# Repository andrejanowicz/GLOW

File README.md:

# GLOW preamp board for G&L L-2000 and L-2500 Tribute basses

</br>

### you might now the situation

>You’re at band rehearsal, playing your beautiful L2000 in active mode with crisp treble boost (that's how its done, right?), as you notice the dreaded hissing of a dying battery. You switch to passive mode with the swiftness of a hungry cheetah, but the guitar player already gives you the look. Of course he has noticed. He always does. You did only pretend to notice the pre CBS mojo of his '62 Strat though. Take that, Mr. all-passive-signal-path.
>
>As the song is done, you put the bass away. No way you’re changing the battery right here on the spot, with all those witnesses. This dirty secret must stay between the L2000 and you, they must not know! They have no idea that this is Leo’s actual masterpiece, not some overpriced 60s guitar. You touch the little switches, toggle them one by one, the click is as satisfying as on the day you brought it home. It takes some time to understand them, sure. To you, they are no mystery. Of course there are a lot of wires needed for all this flexibility, only a fool would not understand that. „Volume - Volume - Tone.. Pathetic!“ you mumble to yourself a little louder than intended. By now the drummer also looks at you. You go home. You wait until everybody is asleep and start silently searching for the screwdriver. You bite your tongue as you open the electronics compartment. You just can’t stand that mess. This instrument deserves better. You change the battery, put the bass aside and check to what dimensions the lead time for Wal MK2‘s has grown by now. You drool over that sweet, clean and well organized electronics box, that PCB: per-fec-tion. If you only bought one eight years ago, when you had the chance. While contemplating live decisions you hear a soft voice: Is everything okay, honey? It’s late, are you looking at bass guitars on the internet again? "Damn right I am, and I think I might have a plan" you say as you look up without blinking your eyes.

## Features

- single PCB with elegant black soldermask
- directly connected toggle switches, no extra wires
- additional single coil setting using only outer coils (K-Mod)
- original preamp circuitry using highest quality components:
- Wima MKP/FKP foil capacitors, Panasonic FC electrolytic capacitors, Yageo 1% resistors
- compatible with original LM4250 or alternatively TL061 op-amps
- fully open source KiCad project (CC BY-NC-SA 4.0)
- fits Tribute models made in Korea and Indonesia (no guarantee)
- banana shaped

## PCB top
</br>
## PCB bottom
</br>
## installed

I give absolutely no guarantee that the PCB and most important the position of the toggle switches will fit your bass. Glow was succesfully installed by me and others in four and five string indonesian and korean Tribute models (L-2000 and L-2500). Fit in USA models is unknown. It does <b>not</b> fit models with sheet metal cover on front/knob side. 
The stock 24mm pots are interfering with GLOW PCB and you need to use 16mm pots with at least 7mm thread length. For more information see BOM document.

## Drill hole position check

You can upfront assess the fit by 3D printing GLOW_test_jig.stl and align the jig with the position of your toggle switches.

## Thanks
This project would have been much harder without the extensive information found on [bassesbyleo.com](https://www.bassesbyleo.com/) .

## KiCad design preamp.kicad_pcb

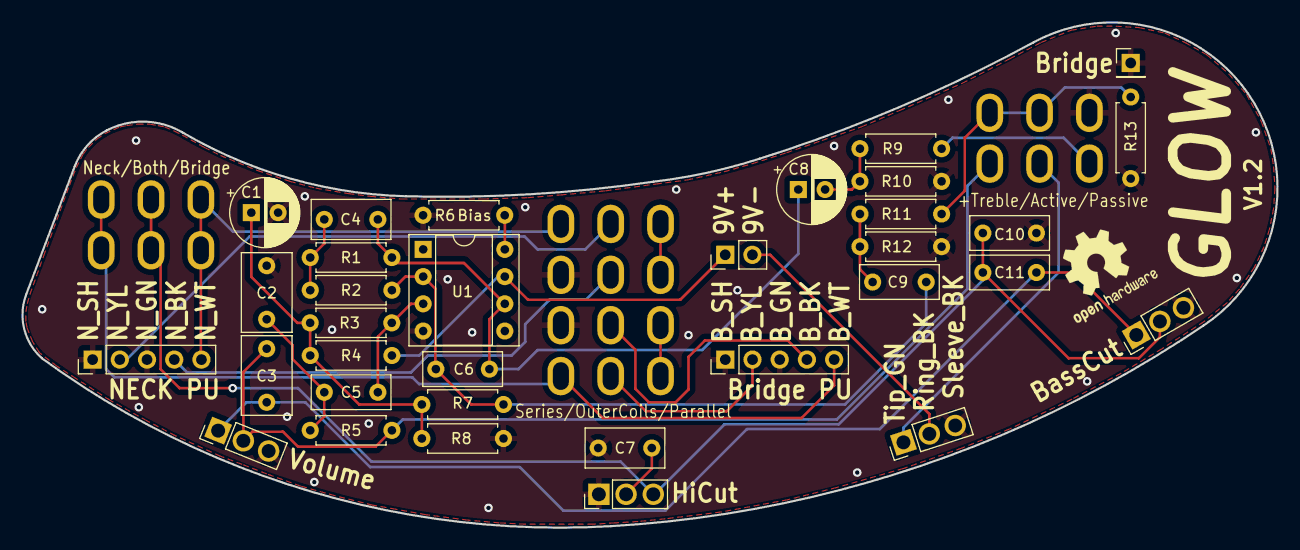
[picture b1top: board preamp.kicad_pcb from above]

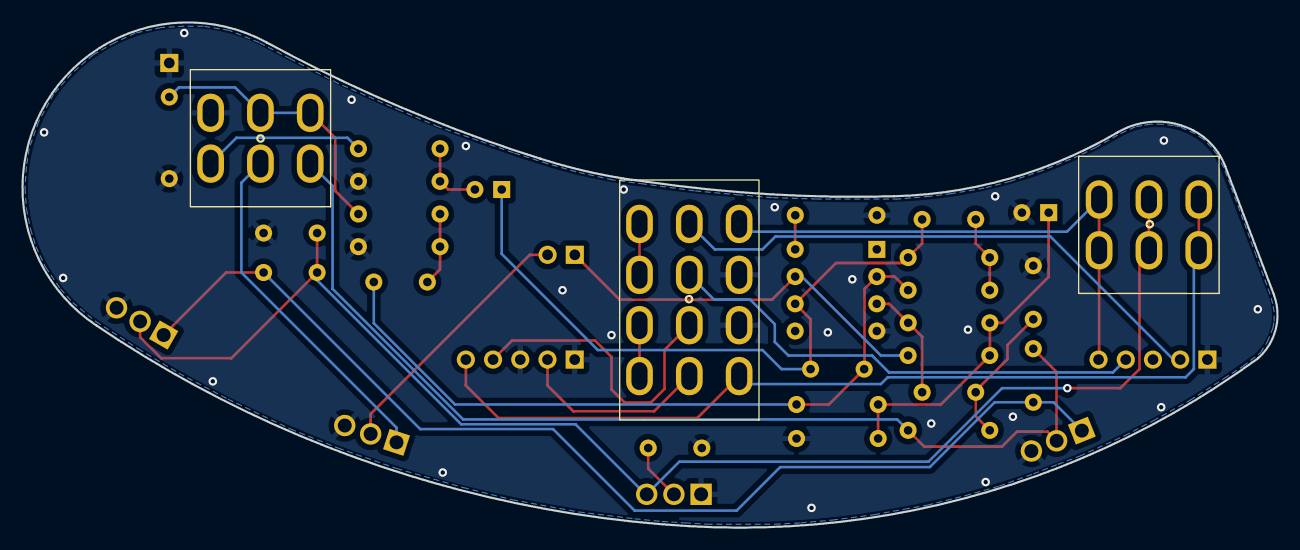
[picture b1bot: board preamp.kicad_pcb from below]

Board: 2 copper layers, 117.1 x 47.1 mm, 36 parts (3 on the bottom side), 27 nets.

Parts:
C1, C8: 10uF; CP_Radial_D6.3mm_P2.50mm
C2, C3: 220pF; C_Rect_L7.2mm_W4.5mm_P5.00mm_FKS2_FKP2_MKS2_MKP2
C4, C7: 47nF; C_Rect_L7.2mm_W3.5mm_P5.00mm_FKS2_FKP2_MKS2_MKP2
C5: 10nF; C_Rect_L7.2mm_W3.0mm_P5.00mm_FKS2_FKP2_MKS2_MKP2
C6, C10: 1nF; C_Rect_L7.2mm_W3.0mm_P5.00mm_FKS2_FKP2_MKS2_MKP2
C9: 15nF; C_Rect_L7.2mm_W3.0mm_P5.00mm_FKS2_FKP2_MKS2_MKP2
C11: 2,2nF; C_Rect_L7.2mm_W3.0mm_P5.00mm_FKS2_FKP2_MKS2_MKP2
J1: Neck; PinHeader_1x05_P2.54mm_Vertical
J2: Bridge; PinHeader_1x05_P2.54mm_Vertical
J3: 9V; PinHeader_1x02_P2.54mm_Vertical
J4: TRS; PinHeader_1x03_P2.54mm_Vertical
J5: Bridge GND; PinHeader_1x01_P2.54mm_Vertical
P1: Volume 250k log; PinHeader_1x03_P2.54mm_Vertical
P2: Hi Cut 250k log; PinHeader_1x03_P2.54mm_Vertical
P3: Bass Cut 1M; PinHeader_1x03_P2.54mm_Vertical
R1, R2: 21.5k; R_Axial_DIN0207_L6.3mm_D2.5mm_P7.62mm_Horizontal
R3, R4, R8: 1M; R_Axial_DIN0207_L6.3mm_D2.5mm_P7.62mm_Horizontal
R5, R9: 1k; R_Axial_DIN0207_L6.3mm_D2.5mm_P7.62mm_Horizontal
R6: 1.5M; R_Axial_DIN0207_L6.3mm_D2.5mm_P7.62mm_Horizontal
R7: 221K; R_Axial_DIN0207_L6.3mm_D2.5mm_P7.62mm_Horizontal
R10: 100k; R_Axial_DIN0207_L6.3mm_D2.5mm_P7.62mm_Horizontal
R11: 10K; R_Axial_DIN0207_L6.3mm_D2.5mm_P7.62mm_Horizontal
R12: 27.4k; R_Axial_DIN0207_L6.3mm_D2.5mm_P7.62mm_Horizontal
R13: 10M; R_Axial_DIN0207_L6.3mm_D2.5mm_P7.62mm_Horizontal
S1, S3: 2PDT ON,ON,ON; DPDT M2044SS1W01
S2: 4PDT ON,ON,ON; 4PDT M2044SS1W01
U1: LM4250; DIP-8_W7.62mm_Socket

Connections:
9V_NEGATIVE: J3.2, J4.2
+9V: J3.1, R4.1, U1.7 (V+)
AUDIO_JACK_SLEEVE_GROUND: C1.2, C2.1, C7.2, C10.1, J1.1, J1.3, J2.1, J2.3, J4.3, J5.1, P1.3, P2.1, P3.3, R6.2, R8.2, R10.1, R12.1, R13.1, S2.4, S2.7, S3.6, U1.4 (V-)
AUDIO_JACK_TIP_SIGNAL: J4.1, S3.2
BRIDGE_OUT: J2.5, S1.1, S1.4, S2.1
B_BLACK: J2.4, S2.5
B_YELLOW: J2.2, S2.2
NECK_OUT: J1.5, S1.3, S1.6, S2.10
N_BLACK: J1.4, S2.8
N_YELLOW: J1.2, S2.11
unnamed: C1.1, R3.1, R4.2, R7.1, R8.1
unnamed: C2.2, C5.1, R5.2
unnamed: C4.1, C6.1, C8.1, R1.2, U1.6
unnamed: C4.2, R1.1, R2.2
unnamed: C5.2, R3.2, U1.3 (+)
unnamed: C6.2, C9.1, R2.1, R7.2, U1.2 (-)
unnamed: C7.1, P2.2
unnamed: C8.2, R9.1, R10.2
unnamed: C9.2, R11.1, R12.2
unnamed: C3.2, C11.2, P1.1, P3.1
unnamed: R6.1, U1.8 (IQ)
unnamed: S2.3, S2.6
unnamed: S2.9, S2.12
PREAMP_IN: C3.1, P1.2, R5.1, S3.1
PREAMP_OUT: R9.2, S3.3
PREAMP_SW: R11.2, R13.2, S3.4, S3.5
PU_OUT: C10.2, C11.1, P2.3, P3.2, S1.2, S1.5

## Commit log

2022-05-04 inital commit
2022-05-04 PCB bottom and top view
2022-05-04 Update README.md
    basic project description
2022-05-04 added 16mm pots to BOM
2022-05-05 added PDF of schematic
2022-05-07 cleaned up Fab layers
2022-05-07 Revert "cleaned up Fab layers"
    This reverts commit a53a61183b3b20636eedd4e96066f84f9d1e0d9c.
2022-05-07 added assembly drawing
2022-05-11 added manual
2022-05-17 updated BOM, included new pots
2022-05-17 updated manual
2022-05-17 added CC BY_NC 4.0 license text
2022-05-29 added test jig

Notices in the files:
preamp.kicad_pcb:
Attribution-NonCommercial-ShareAlike 4.0 CC BY-NC-SA 4.0
